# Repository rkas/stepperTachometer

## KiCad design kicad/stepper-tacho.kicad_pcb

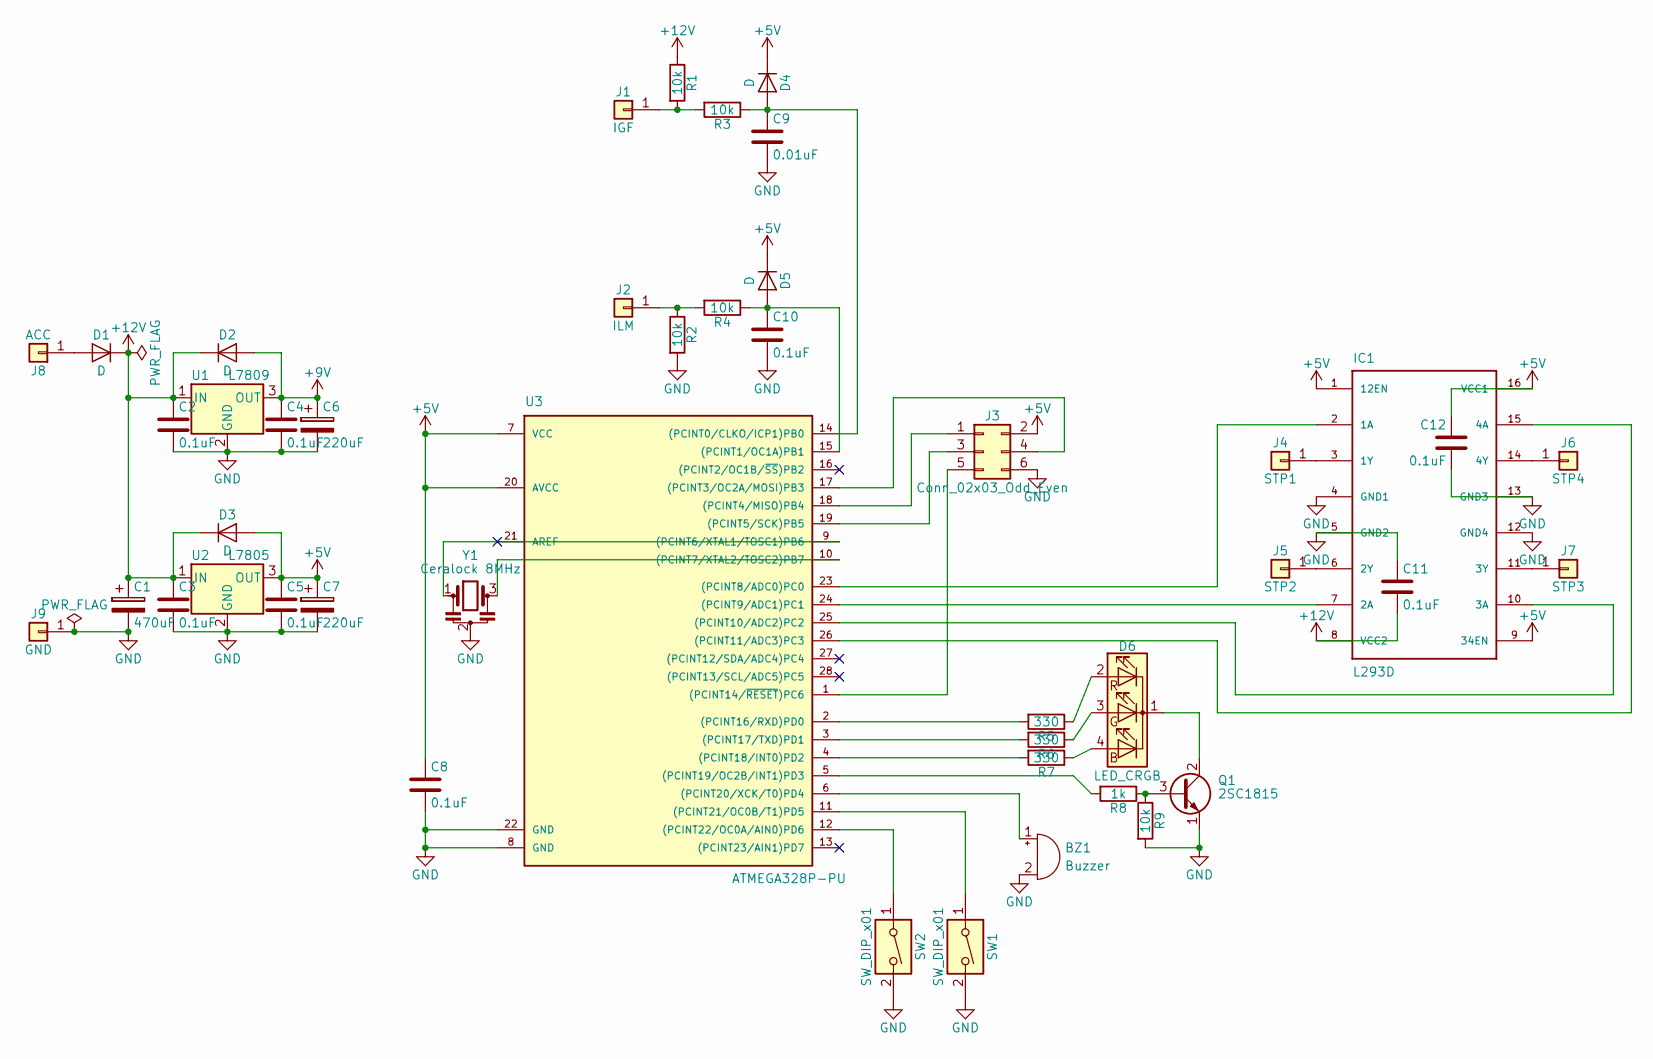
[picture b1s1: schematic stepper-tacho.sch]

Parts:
BZ1: Buzzer; Pin_Header_Straight_1x02_Pitch2.54mm
C1: 470uF; CP_Radial_D10.0mm_P5.00mm
C2, C3, C4, C5, C8, C10, C11, C12: 0.1uF; C_Disc_D5.0mm_W2.5mm_P2.50mm
C6, C7: 220uF; CP_Radial_D8.0mm_P3.50mm
C9: 0.01uF; C_Disc_D5.0mm_W2.5mm_P2.50mm
D1: D; D_A-405_P5.08mm_Vertical_KathodeUp
D2, D3, D4, D5: D; D_T-1_P10.16mm_Horizontal
D6: LED_CRGB; Pin_Header_Straight_1x04_Pitch2.54mm
IC1: L293D; DIP-16_W7.62mm
J1: IGF; Pin_Header_Straight_1x01_Pitch2.54mm
J2: ILM; Pin_Header_Straight_1x01_Pitch2.54mm
J3: Conn_02x03_Odd_Even; Pin_Header_Straight_2x03_Pitch2.54mm
J4: STP1; Pin_Header_Straight_1x01_Pitch2.54mm
J5: STP2; Pin_Header_Straight_1x01_Pitch2.54mm
J6: STP4; Pin_Header_Straight_1x01_Pitch2.54mm
J7: STP3; Pin_Header_Straight_1x01_Pitch2.54mm
J8: ACC; Pin_Header_Straight_1x01_Pitch2.54mm
J9: GND; Pin_Header_Straight_1x01_Pitch2.54mm
Q1: 2SC1815; TO-92_Molded_Narrow
R1, R2, R3, R4, R9: 10k; R_Axial_DIN0207_L6.3mm_D2.5mm_P7.62mm_Horizontal
R5, R6, R7: 330; R_Axial_DIN0207_L6.3mm_D2.5mm_P7.62mm_Horizontal
R8: 1k; R_Axial_DIN0207_L6.3mm_D2.5mm_P7.62mm_Horizontal
SW1, SW2: SW_DIP_x01; Pin_Header_Straight_1x02_Pitch2.54mm
U1: L7809; TO-220-3_Vertical
U2: L7805; TO-220-3_Vertical
U3: ATMEGA328P-PU; DIP-28_W7.62mm
Y1: Ceralock 8MHz; Resonator_muRata_CSTLSxxxG-3pin_w8.0mm_h3.0mm

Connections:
+5V: C5.1, C7.1, C8.1, C12.1, D3.2 (A), D4.1 (K), D5.1 (K), IC1.1 (12EN), IC1.9 (34EN), IC1.16 (VCC1), J3.2, U2.3 (OUT), U3.7 (VCC), U3.20 (AVCC)
+9V: C4.1, C6.1, D2.2 (A), U1.3 (OUT)
+12V: C1.1, C2.1, C3.1, C11.2, D1.1 (K), D2.1 (K), D3.1 (K), IC1.8 (VCC2), R1.1, U1.1 (IN), U2.1 (IN)
GND: BZ1.2 (+), C1.2, C2.2, C3.2, C4.2, C5.2, C6.2, C7.2, C8.2, C9.2, C10.2, C11.1, C12.2, IC1.4 (GND1), IC1.5 (GND2), IC1.12 (GND4), IC1.13 (GND3), J3.6, J9.1, Q1.1 (E), R2.2, R9.2, SW1.2, SW2.2, U1.2 (GND), U2.2 (GND), U3.8 (GND), U3.22 (GND), Y1.2
unnamed: BZ1.1 (-), U3.6 ((PCINT20/XCK/T0)PD4)
unnamed: C9.1, D4.2 (A), R3.1, U3.14 ((PCINT0/CLKO/ICP1)PB0)
unnamed: C10.1, D5.2 (A), R4.1, U3.15 ((PCINT1/OC1A)PB1)
unnamed: D1.2 (A), J8.1
unnamed: D6.1 (K), Q1.2 (C)
unnamed: D6.2 (RA), R5.1
unnamed: D6.3 (GA), R6.1
unnamed: D6.4 (BA), R7.1
unnamed: IC1.2 (1A), U3.23 ((PCINT8/ADC0)PC0)
unnamed: IC1.3 (1Y), J4.1
unnamed: IC1.6 (2Y), J5.1
unnamed: IC1.7 (2A), U3.24 ((PCINT9/ADC1)PC1)
unnamed: IC1.10 (3A), U3.25 ((PCINT10/ADC2)PC2)
unnamed: IC1.11 (3Y), J7.1
unnamed: IC1.14 (4Y), J6.1
unnamed: IC1.15 (4A), U3.26 ((PCINT11/ADC3)PC3)
unnamed: J1.1, R1.2, R3.2
unnamed: J2.1, R2.1, R4.2
unnamed: J3.1, U3.18 ((PCINT4/MISO)PB4)
unnamed: J3.3, U3.19 ((PCINT5/SCK)PB5)
unnamed: J3.4, U3.17 ((PCINT3/OC2A/MOSI)PB3)
unnamed: J3.5, U3.1 ((PCINT14/~RESET~)PC6)
unnamed: Q1.3 (B), R8.1, R9.1
unnamed: R5.2, U3.2 ((PCINT16/RXD)PD0)
unnamed: R6.2, U3.3 ((PCINT17/TXD)PD1)
unnamed: R7.2, U3.4 ((PCINT18/INT0)PD2)
unnamed: R8.2, U3.5 ((PCINT19/OC2B/INT1)PD3)
unnamed: SW1.1, U3.11 ((PCINT21/OC0B/T1)PD5)
unnamed: SW2.1, U3.12 ((PCINT22/OC0A/AIN0)PD6)
unnamed: U3.9 ((PCINT6/XTAL1/TOSC1)PB6), Y1.1
unnamed: U3.10 ((PCINT7/XTAL2/TOSC2)PB7), Y1.3

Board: 2 copper layers, 45 parts (0 on the bottom side), 35 nets, no tracks yet.

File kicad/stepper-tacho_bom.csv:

Reference, Value, Footprint, Datasheet, フィールド4, フィールド5, フィールド6, フィールド7, フィールド8
"U3","ATMEGA328P-PU","Housings_DIP:DIP-28_W7.62mm",""
"U1","L7809","TO_SOT_Packages_THT:TO-220-3_Vertical",""
"U2","L7805","TO_SOT_Packages_THT:TO-220-3_Vertical",""
"C2","0.1uF","Capacitors_THT:C_Disc_D5.0mm_W2.5mm_P2.50mm",""
"C4","0.1uF","Capacitors_THT:C_Disc_D5.0mm_W2.5mm_P2.50mm",""
"C3","0.1uF","Capacitors_THT:C_Disc_D5.0mm_W2.5mm_P2.50mm",""
"C5","0.1uF","Capacitors_THT:C_Disc_D5.0mm_W2.5mm_P2.50mm",""
"C6","220uF","Capacitors_THT:CP_Radial_D8.0mm_P3.50mm",""
"C7","220uF","Capacitors_THT:CP_Radial_D8.0mm_P3.50mm",""
"C1","470uF","Capacitors_THT:CP_Radial_D10.0mm_P5.00mm",""
"C8","0.1uF","Capacitors_THT:C_Disc_D5.0mm_W2.5mm_P2.50mm",""
"J2","ILM","Pin_Headers:Pin_Header_Straight_1x01_Pitch2.54mm",""
"R2","10k","Resistors_THT:R_Axial_DIN0207_L6.3mm_D2.5mm_P7.62mm_Horizontal",""
"R4","10k","Resistors_THT:R_Axial_DIN0207_L6.3mm_D2.5mm_P7.62mm_Horizontal",""
"D5","D","Diodes_THT:D_T-1_P10.16mm_Horizontal",""
"C10","0.1uF","Capacitors_THT:C_Disc_D5.0mm_W2.5mm_P2.50mm",""
"J1","IGF","Pin_Headers:Pin_Header_Straight_1x01_Pitch2.54mm",""
"R1","10k","Resistors_THT:R_Axial_DIN0207_L6.3mm_D2.5mm_P7.62mm_Horizontal",""
"R3","10k","Resistors_THT:R_Axial_DIN0207_L6.3mm_D2.5mm_P7.62mm_Horizontal",""
"D4","D","Diodes_THT:D_T-1_P10.16mm_Horizontal",""
"C9","0.01uF","Capacitors_THT:C_Disc_D5.0mm_W2.5mm_P2.50mm",""
"Y1","Ceralock 8MHz","Crystals:Resonator_muRata_CSTLSxxxG-3pin_w8.0mm_h3.0mm",""
"J3","Conn_02x03_Odd_Even","Pin_Headers:Pin_Header_Straight_2x03_Pitch2.54mm",""
"IC1","L293D","Housings_DIP:DIP-16_W7.62mm","2.44 USD","SOIC-20 STMicroelectronics","L293D","Good","STMicroelectronics","Driver; 36V; Power DIP; 600mA Low LevelO/P; 1.2A O/P High Level; 4 Drivers; 7V"
"C12","0.1uF","Capacitors_THT:C_Disc_D5.0mm_W2.5mm_P2.50mm",""
"C11","0.1uF","Capacitors_THT:C_Disc_D5.0mm_W2.5mm_P2.50mm",""
"J4","STP1","Pin_Headers:Pin_Header_Straight_1x01_Pitch2.54mm",""
"J6","STP4","Pin_Headers:Pin_Header_Straight_1x01_Pitch2.54mm",""
"J7","STP3","Pin_Headers:Pin_Header_Straight_1x01_Pitch2.54mm",""
"J5","STP2","Pin_Headers:Pin_Header_Straight_1x01_Pitch2.54mm",""
"D3","D","Diodes_THT:D_T-1_P10.16mm_Horizontal",""
"D2","D","Diodes_THT:D_T-1_P10.16mm_Horizontal",""
"D1","D","Diodes_THT:D_A-405_P5.08mm_Vertical_KathodeUp",""
"D6","LED_RCBG","Pin_Headers:Pin_Header_Straight_1x04_Pitch2.54mm",""
"R5","330","Resistors_THT:R_Axial_DIN0207_L6.3mm_D2.5mm_P7.62mm_Horizontal",""
"R6","330","Resistors_THT:R_Axial_DIN0207_L6.3mm_D2.5mm_P7.62mm_Horizontal",""
"R7","330","Resistors_THT:R_Axial_DIN0207_L6.3mm_D2.5mm_P7.62mm_Horizontal",""
"Q1","2SC1815","TO_SOT_Packages_THT:TO-92_Molded_Narrow",""
"R8","1k","Resistors_THT:R_Axial_DIN0207_L6.3mm_D2.5mm_P7.62mm_Horizontal",""
"R9","10k","Resistors_THT:R_Axial_DIN0207_L6.3mm_D2.5mm_P7.62mm_Horizontal",""
"BZ1","Buzzer","Pin_Headers:Pin_Header_Straight_1x02_Pitch2.54mm",""
"SW1","SW_DIP_x01","Pin_Headers:Pin_Header_Straight_1x02_Pitch2.54mm",""
"SW2","SW_DIP_x01","Pin_Headers:Pin_Header_Straight_1x02_Pitch2.54mm",""
"J8","ACC","Pin_Headers:Pin_Header_Straight_1x01_Pitch2.54mm",""
"J9","GND","Pin_Headers:Pin_Header_Straight_1x01_Pitch2.54mm",""

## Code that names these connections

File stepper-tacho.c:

/*
Stepper Tachometer for ATmega168P & X27.168 (& L293D)

PC0	->	Stepper1
PC1 ->	Stepper2
PC2 ->	Stepper3
PC3 ->	Stepper4
PB0	->	Input(REV)	ICP1
PB1 ->	Input(ILM)
PD0 ->	LED(RED)
PD1 ->	LED(GRN)
PD2 ->	LED(BLU)
PD3 ->	PWM(LED)		OC2B
PD4	->	Buzzer
PD5	->	Button1(Pulled-up)
PD6	->	Button2(Pulled-up)
*/

#define F_CPU 1000000UL

#include <avr/io.h>
#include <avr/interrupt.h>
#include <util/delay.h>
#include <stdio.h>
#include <stdlib.h>

#define BLUZONE_RPM 2800
#define GRNZONE_RPM 3400
#define YELZONE_RPM 6800
#define REDZONE_RPM 7400
#define DIMMER_DUTY	32
#define VAL_DIVBY_TP_US 30000000
// RPM = (1 / 2) * ((1 / timePeriod_us) * 1000 * 1000 * 60); //
//          ↑ クランク1回転で2パルス出るため                       //
//     = 30000000 / timePeriod_us                            //

#define NUM_STEPS_ZERO_OFFSET 100	//モーター内蔵ストッパーと文字盤の0点との差(1ステップ=0.333deg)
#define DELAY_STEPS_US 1500	//原点出し時の駆動周期
#define NUM_SAMPLE 5	//パルス幅測定値の移動平均を求めるときに使うサンプル数
#define PLAY_OF_POSITION 0	//targetPositionとcurrentPositionとの許容遊び幅

#define TIMEPERIOD_US_MIN 1832	//これより速い周期は考えない(オーバーフロー対策)
#define NUM_VELOCITIES 48	//配列velocityToOCR0ATableのサイズ。何ステップかけて最低速から最高速まで加減速するか

#define OFF 0
#define ON	1
#define BLU 1
#define GRN 2
#define YEL 3
#define RED 4


// Global variable declaration //

volatile int currentState = 0;	//0-6
volatile int currentPosition = 0;	//0-945 315/(60/180)
volatile int targetPosition = 0;	//0-945
const int pulseStateTable[6] = {
	//3210
	0b0110,
	0b0100,
	0b0001,
	0b1001,
	0b1000,
	0b0010,
};

volatile int velocity = 0;	// -(NUM_VELOCITIES-1)~0~(NUM_VELOCITIES-1)
const unsigned char velocityToOCR0ATable[NUM_VELOCITIES] = {	//Unit: 1 * 64 [us]
	40,  39,  38,  38,  37,  36,  36,  35,
	34,  34,  33,  32,  32,  31,  31,  30,
	29,  29,  28,  27,  27,  26,  25,  25,
	24,  24,  23,  22,  22,  21,  20,  20,
	19,  18,  18,  17,  17,  16,  15,  15,
	14,  13,  13,  12,  11,  11,  10,  10
};

volatile unsigned int countTIMER1Overflow = 0;	//TIMER1のオーバーフロー回数
volatile unsigned long timePeriod_us = 1000000000;	//入力パルスの周期

unsigned char ledBrightness = 32;	//


// Proto-type declaration //

void portInit();
void timerInit();
int myAbs(int x);
void stepUp();
void stepDown();
void zeroCariblate();
int getPositionFromRpm(unsigned int rpm);
void led(int color);
void beep(int state);
int isIlmOn();
void openingCelemony();


// Interrupt service routine //

ISR(TIMER0_COMPA_vect){
	if (targetPosition > (945 - NUM_STEPS_ZERO_OFFSET)) {targetPosition = (945 - NUM_STEPS_ZERO_OFFSET);}
	//if (targetPosition < 0) {targetPosition = 0;}
	if ((myAbs(targetPosition - currentPosition)) < (myAbs(velocity))) {	//currentPositionがtargetPositionの近くだったら
		if (velocity < 0) {	//減速(velocityを0に近づける)
			velocity++;
		} else if (velocity > 0) {
			velocity--;
		}
	} else {	//targetPositionが十分遠ければ
		if ((currentPosition < targetPosition) && (velocity < (NUM_VELOCITIES - 1))) {	//CWに加速(velocityの絶対値を増加)
			velocity++;
		} else if ((currentPosition > targetPosition) && (velocity > -(NUM_VELOCITIES - 1))) {	//CCWに加速
			velocity--;
		}
	}
	if ((myAbs(currentPosition - targetPosition)) > PLAY_OF_POSITION) {
		if (velocity > 0) {
			stepUp();
		} else if (velocity < 0) {
			stepDown();
		}
	}
	OCR0A = velocityToOCR0ATable[myAbs(velocity)];	//次に自身が呼び出されるまでの時間を設定
}

ISR(TIMER1_CAPT_vect){	//パルス立ち下がり時
	TCNT1 = 0;
	timePeriod_us = countTIMER1Overflow * 65536 + ICR1;
	countTIMER1Overflow = 0;
}

ISR(TIMER1_OVF_vect){
	countTIMER1Overflow++;
}


int main(void){
	cli();
	portInit();
	timerInit();
	zeroCariblate();
	sei();

	_delay_ms(100);	//wait for pulse coming
	if (timePeriod_us == 1000000000) {	//no pulse
		openingCelemony();
	}

	unsigned long timePeriod_us_history[NUM_SAMPLE];
	for (int i = 0; i < NUM_SAMPLE; i++) {timePeriod_us_history[i] = 1000000000;}
	unsigned long timePeriod_us_sum;
	unsigned long timePeriod_us_mean;
	unsigned int rpm = 0;
	int j = 0;
	while (1) {
		// パルス周期の移動平均をとる (最大値と最小値は除いて計算) //
		if (timePeriod_us < TIMEPERIOD_US_MIN) {timePeriod_us = TIMEPERIOD_US_MIN;}
		timePeriod_us_history[j] = timePeriod_us;
		j++;	if (j == NUM_SAMPLE) {j = 0;}
		timePeriod_us_sum = 0;
		unsigned long min, max;
		min = max = timePeriod_us_history[j];
		for (int i = 0; i < NUM_SAMPLE; i++) {
			timePeriod_us_sum += (timePeriod_us_history[i]);
			if (timePeriod_us_history[i] < min) {min = timePeriod_us_history[i];}
			if (timePeriod_us_history[i] > max) {max = timePeriod_us_history[i];}
		}
		timePeriod_us_mean = (timePeriod_us_sum - min - max) / (NUM_SAMPLE - 2);
		// パルス周期の平均値から回転数を算出 //
		rpm = VAL_DIVBY_TP_US / timePeriod_us_mean;

		if (countTIMER1Overflow > 4) {rpm = 0;}	//114rpm以下(0.26秒以上無入力)で0rpm扱い
		targetPosition = getPositionFromRpm(rpm);

		if (rpm > REDZONE_RPM) {
			led(RED);
		} else if (rpm > YELZONE_RPM) {
			led(YEL);
		} else if (rpm > GRNZONE_RPM) {
			led(GRN);
		} else if (rpm > BLUZONE_RPM) {
			led(BLU);
		} else {
			led(OFF);
		}

		if (isIlmOn()) {
			OCR2B = DIMMER_DUTY;
		} else {
			OCR2B = 255;
		}
	}
}


// Funcion definidion //

void portInit(){
	DDRC  = 0b00001111;	//Stepper1~4
	DDRB  = 0b00000000;	//Input(REV, ILM)
	DDRD  = 0b00011111;	//LED(R,G,B), PWM, Buzz, Btn1~2
	PORTC = 0b11110000;
	PORTB = 0b11111100;
	PORTD = 0b11100000;	//Btn1~2 pull-up
}

void timerInit(){
	// TIMER0 //	(For Stepper Driving)
	//タイマ／カウンタ0制御レジスタA
	//         ++------ COM1A1:COM1A0
	//         ||++---- COM1B1:COM1B0
	//         ||||  ++ WGM01:WGM00     波形生成種別(3bitの下位2bit)
	TCCR0A = 0b00000010;

	//タイマ／カウンタ0制御レジスタB
	//         +------- FOC0A						0?
	//         |+------ FOC0B						0?
	//         ||  +--- WGM02						波形生成種別(3bitの上位1bit)
	//         ||  |+++ CS02:CS01:CS00	分周
	TCCR0B = 0b00000011;

	//StepperDrivingSpeed (Smaller is higher speed)
	OCR0A = velocityToOCR0ATable[0];
	// 1MHz/(64*(1+OCR0A)) [Hz]
	// 1/(1MHz/(64*(1+OCR0A))) [sec]
	// must be 8, 10, or more?

	//タイマ／カウンタ0割り込みマスクレジスタ
	//              +-- OCIE0B
	//              |+- OCIE0A
	//              ||+ TOIE0
	TIMSK0 = 0b00000010;


	// TIMER1 //	(For Rev Pulse Measuring)
	//タイマ／カウンタ1制御レジスタA
	//         ++------ COM1A1:COM1A0
	//         ||++---- COM1B1:COM1B0
	//         ||||  ++ WGM11:WGM10     波形生成種別(4bitの下位2bit)
	TCCR1A = 0b00000000;

	//タイマ／カウンタ1制御レジスタB
	//         +------- ICNC1
	//         |+------ ICES1
	//         || ++--- WGM13:WGM12     波形生成種別(4bitの上位2bit)
	//         || ||+++ CS12:CS11:CS10  分周
	TCCR1B = 0b00000001;

	//タイマ／カウンタ1割り込みマスクレジスタ
	//           +----- ICIE1
	//           |  +-- OCIE1B
	//           |  |+- OCIE1A
	//           |  ||+ TOIE1
	TIMSK1 = 0b00100001;


	// TIMER2 //	(For LED PWM)
	//タイマ／カウンタ2制御レジスタA
	//         ++------ COM2A1:COM2A0
	//         ||++---- COM2B1:COM2B0
	//         ||||  ++ WGM21:WGM20     波形生成種別(3bitの下位2bit)
	TCCR2A = 0b00110011;

	//タイマ／カウンタ0制御レジスタB
	//         +------- FOC2A						0?
	//         |+------ FOC2B						0?
	//         ||  +--- WGM22						波形生成種別(3bitの上位1bit)
	//         ||  |+++ CS22:CS21:CS20	分周
	TCCR2B = 0b00000001;

	//LED PWM-Duty
	OCR2B = 255;
	// Duty[%] = OCR2B / 255 * 100

	//タイマ／カウンタ2割り込みマスクレジスタ
	//              +-- OCIE2B
	//              |+- OCIE2A
	//              ||+ TOIE2
	TIMSK2 = 0b00000000;
}

int myAbs(int x){
	if (x < 0) {
		return -x;
	} else {
		return x;
	}
}

/* 時計方向に1ステップ進める */
void stepUp(){
	currentPosition++;
	currentState = currentPosition % 6;
	PORTC = pulseStateTable[currentState];
}

/* 反時計方向に1ステップ戻す */
void stepDown(){
	currentPosition--;
	currentState = currentPosition % 6;
	PORTC = pulseStateTable[currentState];
}

void zeroCariblate(){
	cli();
	currentPosition = 1000;
	for (int i = 0; i < 1000; i++) {
		stepDown();
		_delay_us(DELAY_STEPS_US);
	}
	for (int i = 0; i < NUM_STEPS_ZERO_OFFSET; i++) {
		stepUp();
		_delay_us(DELAY_STEPS_US);
	}
	currentPosition = 0;
}

int getPositionFromRpm(unsigned int rpm){
	return (rpm / 10);
}

void led(int color){
	switch (color) {
		case 1:	//BLU
			PORTD &= 0b11111100;
			PORTD |= 0b00000100;
			break;
		case 2:	//GRN
			PORTD &= 0b11111010;
			PORTD |= 0b00000010;
			break;
		case 3:	//YEL
			PORTD &= 0b11111011;
			PORTD |= 0b00000011;
			break;
		case 4:	//RED
			PORTD &= 0b11111001;
			PORTD |= 0b00000001;
			break;
		default:	//OFF
			PORTD &= 0b11111000;
	}
}

void beep(int state){
	if (state) {
		PORTD |= 0b00010000;
	} else {
		PORTD &= 0b11101111;
	}
}

int isIlmOn(){
	return (PINB & 0b00000010);
}

void openingCelemony(){
	const int zoneRpmTable[5] = {0, BLUZONE_RPM, GRNZONE_RPM, YELZONE_RPM, REDZONE_RPM};
	for (int i = 1; i <=4; i++) {
		targetPosition = getPositionFromRpm(zoneRpmTable[i]);
		while (currentPosition != targetPosition);
		led(i);
		_delay_ms(250);
		led(OFF);
	}
	targetPosition = 0;
	while (currentPosition != targetPosition);
}

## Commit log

2018-04-18 add kicad
2018-04-19 pcb配置
2018-04-20 first branch
